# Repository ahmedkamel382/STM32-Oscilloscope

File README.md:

# ⚡ Digital Storage Oscilloscope (STM32F401)

A high-performance, low-cost Digital Storage Oscilloscope (DSO) engineered from the component level up. Built around the **STM32F401 "Black Pill"**, this project bridges embedded hardware and modern data science by combining a custom Analog Front-End (AFE), deterministic DMA-paced sampling, high-speed USB-CDC telemetry, and an offline Machine Learning waveform classifier.

This project was developed for the **Embedded Systems (ECE5206)** course at the **Arab Academy for Science, Technology and Maritime Transport (AASTMT)**, supervised by **Dr. Amr Fahmy**.

---

## 🚀 Key Features

* **Bipolar Signal Acquisition:** A custom analog conditioning circuit featuring a 1.65V virtual ground allows the single-supply microcontroller ADC to safely read alternating current (AC) waveforms.
* **Active Hardware Protection:** Bipolar Junction Transistor (BJT) clamping arrays (`2N3904` / `2N3906`) actively protect the STM32 silicon from over-voltage and negative voltage spikes.
* **Deterministic Firmware Architecture:** Hardware Timer 2 (`TIM2`) strictly paces ADC conversions, completely bypassing software polling delays.
* **Zero-Loss Data Capture:** Direct Memory Access (DMA) utilizing a Ping-Pong (Half/Full) buffering strategy ensures continuous, uninterrupted sampling while the CPU processes data.
* **High-Speed USB Streaming:** A custom USB-CDC pipeline streams raw binary data (736-byte packets) to the host PC, vastly outperforming standard UART communication.
* **Edge AI Classification:** A fully offline `scikit-learn` Random Forest machine learning model analyzes live mathematical features to automatically classify incoming signals (`Sine`, `Square`, `Triangle`, `Noise`, or `DC`).
* **Zero-Lag Desktop UI:** A multi-threaded Python companion application built with `PyQtGraph` delivers 60-FPS real-time rendering alongside an embedded SQLite database for waveform logging.

---

## 🧰 Technology Stack

### Hardware

* **Microcontroller:** STM32F401CCU6 (`84 MHz Core`, `48 MHz USB`)
* **Local Display:** 240×240 ST7789 TFT Display (`SPI`)
* **Analog Front-End:** Precision `33kΩ / 10kΩ` attenuation networks with `2N3904/06` hardware clamps
* **PCB Design:** Custom single-sided PCB routed in KiCad with dedicated power-rail decoupling

### Software & Firmware

* **Embedded Development:** C/C++, STM32CubeIDE (`HAL` & `LL Drivers`)
* **Desktop Application:** Python 3, PyQtGraph, PyQt5, SQLite3
* **Machine Learning:** `scikit-learn`, `numpy`, `joblib`

> The AI classifier was trained on approximately **6,000 synthesized waveforms**.

---

## 📊 Hardware Specifications & Limits

| Specification | Value | Notes |
|---|---|---|
| **Max Input Voltage** | ~ `-5.44V` to `+8.74V` | Scaled via a `0.1315` attenuation factor |
| **Max Sampling Rate** | ~ `1.56 Msps` | ADCCLK pushed to `42 MHz (DIV2)` |
| **Practical Bandwidth** | ~ `150 kHz` | Based on requiring 10 data points per wave cycle |
| **Hardware Filter** | RC Low-Pass | V1.0 uses a `33pF` capacitor (`102 MHz` cutoff). V2.0 recommends a `4.7nF` capacitor to align the anti-alias cutoff to approximately `720 kHz`. |

---

## ⚙️ Getting Started

### 1. Hardware Setup

1. Assemble the Analog Front-End using the provided KiCad schematics located in:

```text
/Hardware Design
```

2. Ensure proper grounding between the device under test (for example, an ICL8038 signal generator) and the STM32.

3. Connect the STM32 board to your PC using a USB Type-C cable.

---

### 2. Firmware Flashing

1. Open the project using **STM32CubeIDE**.
2. Build the firmware.
3. Flash the firmware to the STM32F401 using an **ST-Link V2** programmer.

---

### 3. Running the Desktop Application

Ensure Python 3 is installed on your system.

Navigate to the desktop application directory and install the dependencies:

```bash
cd dso_pc
pip install -r requirements.txt
```

Launch the desktop UI:

```bash
python dso_app.py
```

> The AI classifier (`dso_model.joblib`) is pre-trained.
>
> If you wish to retrain the model using different parameters, execute:
>
> ```bash
> python train_model.py
> ```
>
> before launching the application.

---

## 👨‍💻 Project Team

### Ahmed Khalid Mohamed

* Lead Analog HW & USB Architect
* 1.65V Virtual Ground & Attenuation Mathematics
* High-Speed USB-CDC Binary Pipeline
* Python Packet Decoding (`dso_protocol.py`)

### Adel Alaa

* Lead Display Driver & AI Engineer
* ST7789 High-Speed Column-Redraw Renderer
* KiCad PCB Routing & Hardware Decoupling
* Live Machine Learning UI Integration

### Bassel Adel

* Lead ADC Firmware & PC UI Engineer
* TIM2-Paced Hardware ADC Triggering
* DMA Ping-Pong Buffering Architecture
* Multithreaded PyQtGraph Desktop UI

### Omar Abdel Nasser Omar

* Lead DSP Firmware & Database Engineer
* Peak-Hold & Interpolation DSP Algorithms
* SQLite Waveform Database Logging
* Random Forest AI Model Training

---

## 📝 License & Academic Disclaimer

This repository contains academic coursework and is provided **as-is** for educational purposes. Do **not** connect this device directly to mains AC voltage or high-voltage circuits without proper industrial isolation and safety equipment.

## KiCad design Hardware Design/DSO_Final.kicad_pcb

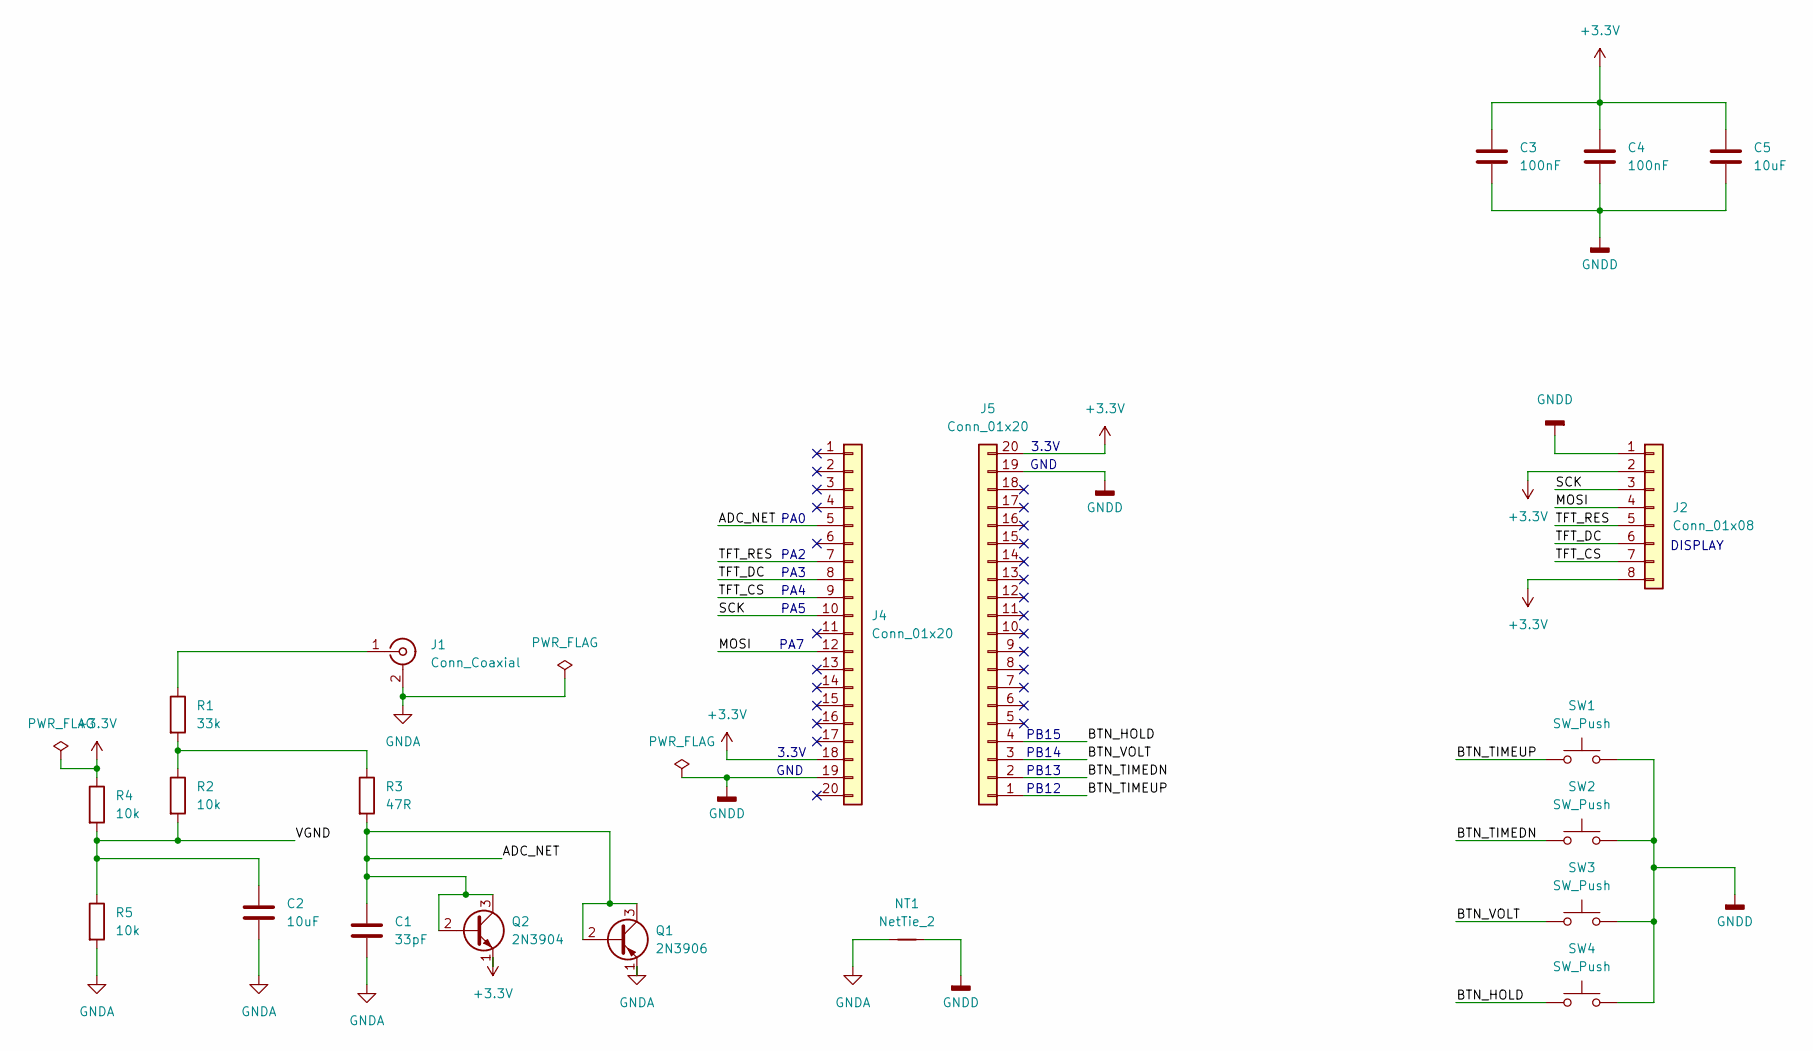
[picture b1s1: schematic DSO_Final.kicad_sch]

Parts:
C1: 33pF; C_Disc_D5.0mm_W2.5mm_P5.00mm
C2, C5: 10uF; CP_Radial_D5.0mm_P2.50mm
C3, C4: 100nF; C_Disc_D5.0mm_W2.5mm_P5.00mm
J1: Conn_Coaxial; BNC_TEConnectivity_1478035_Horizontal
J2: Conn_01x08; PinHeader_1x08_P2.54mm_Vertical
J4, J5: Conn_01x20; PinHeader_1x20_P2.54mm_Vertical
NT1: NetTie_2; NetTie-2_SMD_Pad0.5mm
Q1: 2N3906; TO-92_Inline_Wide
Q2: 2N3904; TO-92_Inline_Wide
R1: 33k; R_Axial_DIN0207_L6.3mm_D2.5mm_P10.16mm_Horizontal
R2, R4, R5: 10k; R_Axial_DIN0207_L6.3mm_D2.5mm_P10.16mm_Horizontal
R3: 47R; R_Axial_DIN0207_L6.3mm_D2.5mm_P10.16mm_Horizontal
SW1, SW2, SW3, SW4: SW_Push; SW_PUSH_6mm

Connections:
+3.3V: C3.1, C4.1, C5.1, J2.2, J2.8, J4.18, J5.20, Q2.1 (E), R4.1
/ADC_NET: C1.1, J4.5, Q1.2 (B), Q1.3 (C), Q2.2 (B), Q2.3 (C), R3.2
/BTN_HOLD: J5.4, SW4.1
/BTN_TIMEDN: J5.2, SW2.1
/BTN_TIMEUP: J5.1, SW1.1
/BTN_VOLT: J5.3, SW3.1
/MOSI: J2.4, J4.12
/SCK: J2.3, J4.10
/TFT_CS: J2.7, J4.9
/TFT_DC: J2.6, J4.8
/TFT_RES: J2.5, J4.7
/VGND: C2.1, R2.2, R4.2, R5.1
GNDA: C1.2, C2.2, J1.2 (Ext), NT1.1, Q1.1 (E), R5.2
GNDD: C3.2, C4.2, C5.2, J2.1, J4.19, J5.19, NT1.2, SW1.2, SW2.2, SW3.2, SW4.2
unnamed: J1.1 (In), R1.1
unnamed: R1.2, R2.1, R3.1

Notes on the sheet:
3.3V
PA7
PA0
PB14
DISPLAY
GND
PB13
PB12
PA5
PB15
PA4
PA3
PA2

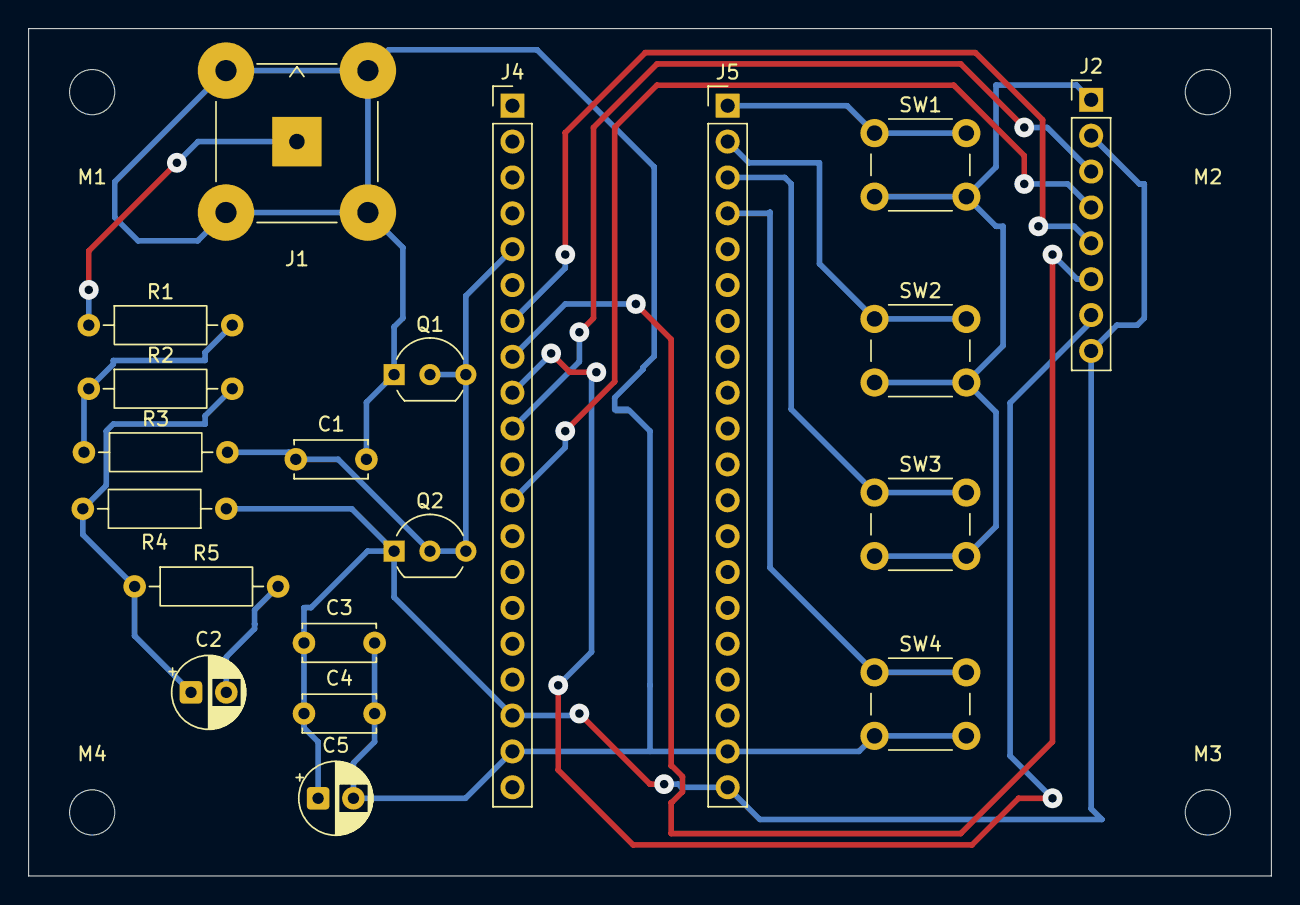
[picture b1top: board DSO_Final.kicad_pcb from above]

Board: 2 copper layers, 88.0 x 60.0 mm, 25 parts (1 on the bottom side), 16 nets.

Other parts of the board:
M1, M2, M3, M4: MountingHole_3.2mm_M3

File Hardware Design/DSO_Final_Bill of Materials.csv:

"Reference","Qty","Value","DNP","Exclude from BOM","Exclude from Board","Footprint","Datasheet"
"C1","1","33pF","","","","Capacitor_THT:C_Disc_D5.0mm_W2.5mm_P5.00mm",""
"C2,C5","2","10uF","","","","Capacitor_THT:CP_Radial_D5.0mm_P2.50mm",""
"C3,C4","2","100nF","","","","Capacitor_THT:C_Disc_D5.0mm_W2.5mm_P5.00mm",""
"J1","1","Conn_Coaxial","","","","Connector_Coaxial:BNC_TEConnectivity_1478035_Horizontal",""
"J2","1","Conn_01x08","","","","Connector_PinHeader_2.54mm:PinHeader_1x08_P2.54mm_Vertical",""
"J4,J5","2","Conn_01x20","","","","Connector_PinHeader_2.54mm:PinHeader_1x20_P2.54mm_Vertical",""
"Q1","1","2N3906","","","","Package_TO_SOT_THT:TO-92_Inline_Wide","https://www.onsemi.com/pub/Collateral/2N3906-D.PDF"
"Q2","1","2N3904","","","","Package_TO_SOT_THT:TO-92_Inline_Wide","https://www.onsemi.com/pub/Collateral/2N3903-D.PDF"
"R1","1","33k","","","","Resistor_THT:R_Axial_DIN0207_L6.3mm_D2.5mm_P10.16mm_Horizontal",""
"R2,R4,R5","3","10k","","","","Resistor_THT:R_Axial_DIN0207_L6.3mm_D2.5mm_P10.16mm_Horizontal",""
"R3","1","47R","","","","Resistor_THT:R_Axial_DIN0207_L6.3mm_D2.5mm_P10.16mm_Horizontal",""
"SW1,SW2,SW3,SW4","4","SW_Push","","","","Button_Switch_THT:SW_PUSH_6mm",""

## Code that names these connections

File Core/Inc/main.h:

/* USER CODE BEGIN Header */
/**
  ******************************************************************************
  * @file           : main.h
  * @brief          : Header for main.c file.
  *                   This file contains the common defines of the application.
  ******************************************************************************
  * @attention
  *
  * Copyright (c) 2026 STMicroelectronics.
  * All rights reserved.
  *
  * This software is licensed under terms that can be found in the LICENSE file
  * in the root directory of this software component.
  * If no LICENSE file comes with this software, it is provided AS-IS.
  *
  ******************************************************************************
  */
/* USER CODE END Header */

/* Define to prevent recursive inclusion -------------------------------------*/
#ifndef __MAIN_H
#define __MAIN_H

#ifdef __cplusplus
extern "C" {
#endif

/* Includes ------------------------------------------------------------------*/
#include "stm32f4xx_hal.h"

/* Private includes ----------------------------------------------------------*/
/* USER CODE BEGIN Includes */

/* USER CODE END Includes */

/* Exported types ------------------------------------------------------------*/
/* USER CODE BEGIN ET */

/* USER CODE END ET */

/* Exported constants --------------------------------------------------------*/
/* USER CODE BEGIN EC */

/* USER CODE END EC */

/* Exported macro ------------------------------------------------------------*/
/* USER CODE BEGIN EM */

/* USER CODE END EM */

/* Exported functions prototypes ---------------------------------------------*/
void Error_Handler(void);

/* USER CODE BEGIN EFP */

/* USER CODE END EFP */

/* Private defines -----------------------------------------------------------*/
#define LED_Pin GPIO_PIN_13
#define LED_GPIO_Port GPIOC
#define TFT_RST_Pin GPIO_PIN_2
#define TFT_RST_GPIO_Port GPIOA
#define TFT_DC_Pin GPIO_PIN_3
#define TFT_DC_GPIO_Port GPIOA
#define TFT_CS_Pin GPIO_PIN_4
#define TFT_CS_GPIO_Port GPIOA
#define BTN_TIMEUP_Pin GPIO_PIN_12
#define BTN_TIMEUP_GPIO_Port GPIOB
#define BTN_TIMEDN_Pin GPIO_PIN_13
#define BTN_TIMEDN_GPIO_Port GPIOB
#define BTN_VOLT_Pin GPIO_PIN_14
#define BTN_VOLT_GPIO_Port GPIOB
#define BTN_HOLD_Pin GPIO_PIN_15
#define BTN_HOLD_GPIO_Port GPIOB

/* USER CODE BEGIN Private defines */

/* USER CODE END Private defines */

#ifdef __cplusplus
}
#endif

#endif /* __MAIN_H */

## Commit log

2026-06-03 Added new UI
2026-06-03 UI Changes
2026-06-04 Added UI for PC, include KiCad designs and Gerber Files
2026-06-04 Added ReadMe File
2026-06-04 Added README.md
2026-06-04 Add README for Digital Storage Oscilloscope project
    This README provides an overview of the Digital Storage Oscilloscope project, including its features, technology stack, hardware specifications, setup instructions, and project team.
2026-06-04 Fixed README.md
2026-06-07 Small Changes
2026-06-07 Small Changes 2
